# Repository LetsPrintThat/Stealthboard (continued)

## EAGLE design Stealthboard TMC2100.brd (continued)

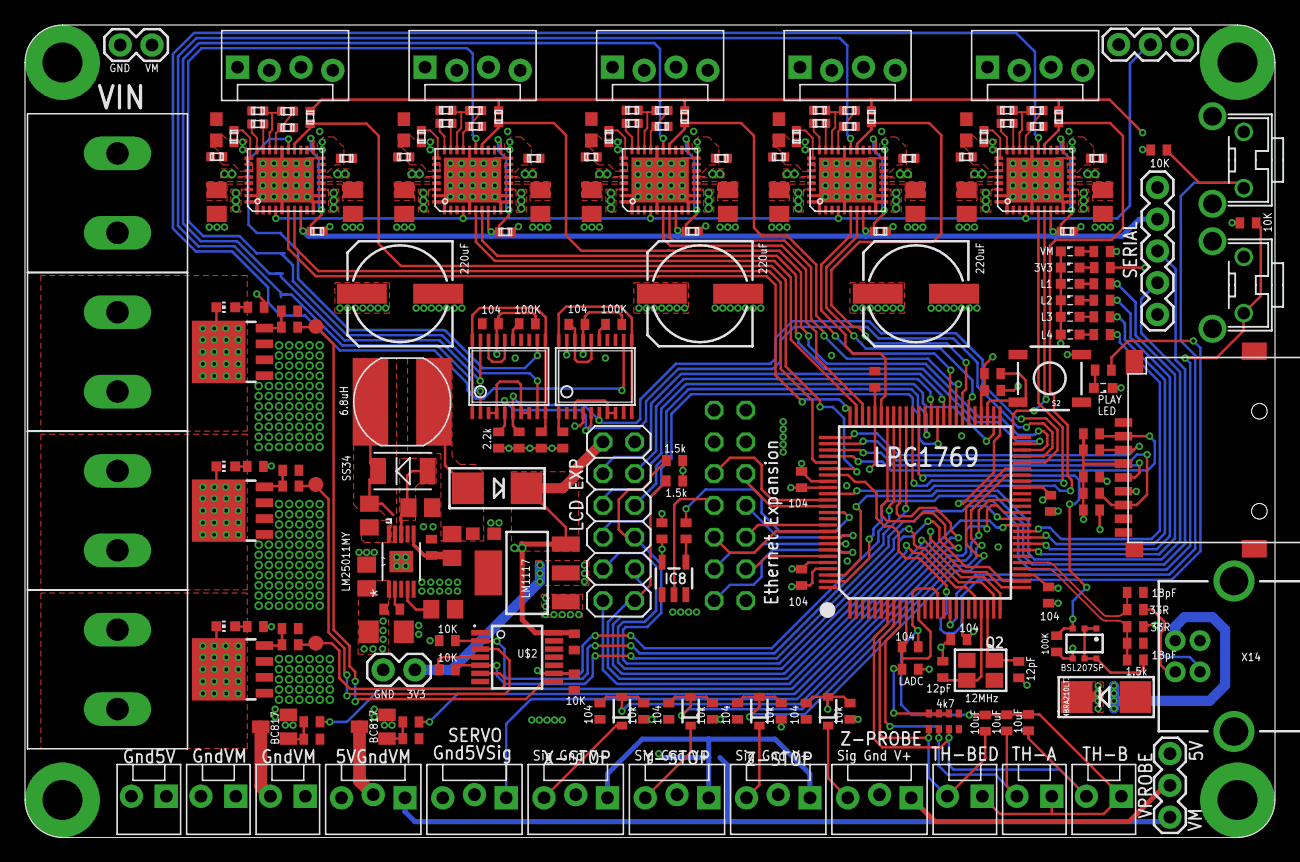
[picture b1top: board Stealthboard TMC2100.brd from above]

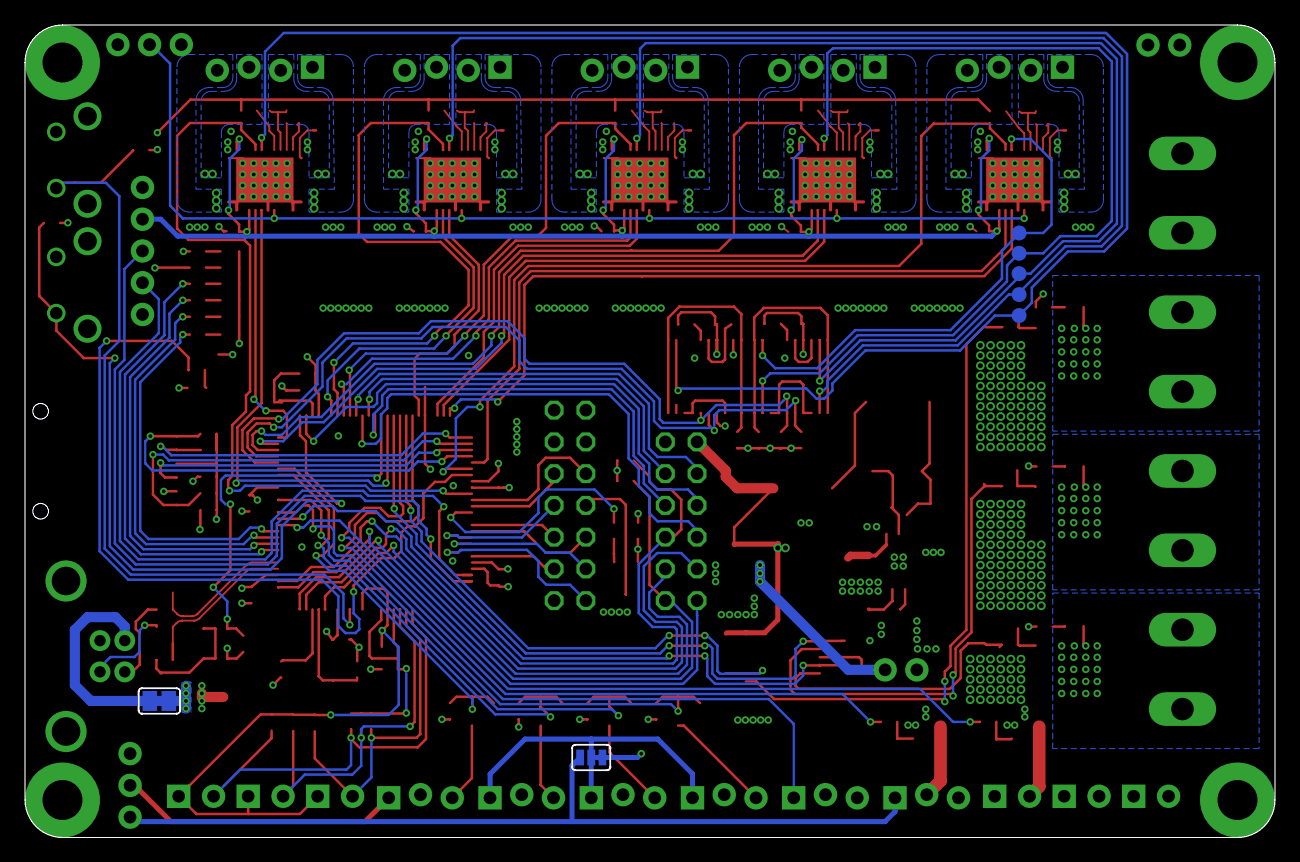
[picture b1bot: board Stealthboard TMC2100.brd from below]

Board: 4 copper layers, 100.0 x 65.0 mm, 225 parts (8 on the bottom side), 165 nets.

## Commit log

2017-04-29 Pre-Production .sch and .brd files
    These files are Pre-Production and should be used at your own risk. This version of Stealthboard contains TMC 2100 drivers and will not be the final version.
